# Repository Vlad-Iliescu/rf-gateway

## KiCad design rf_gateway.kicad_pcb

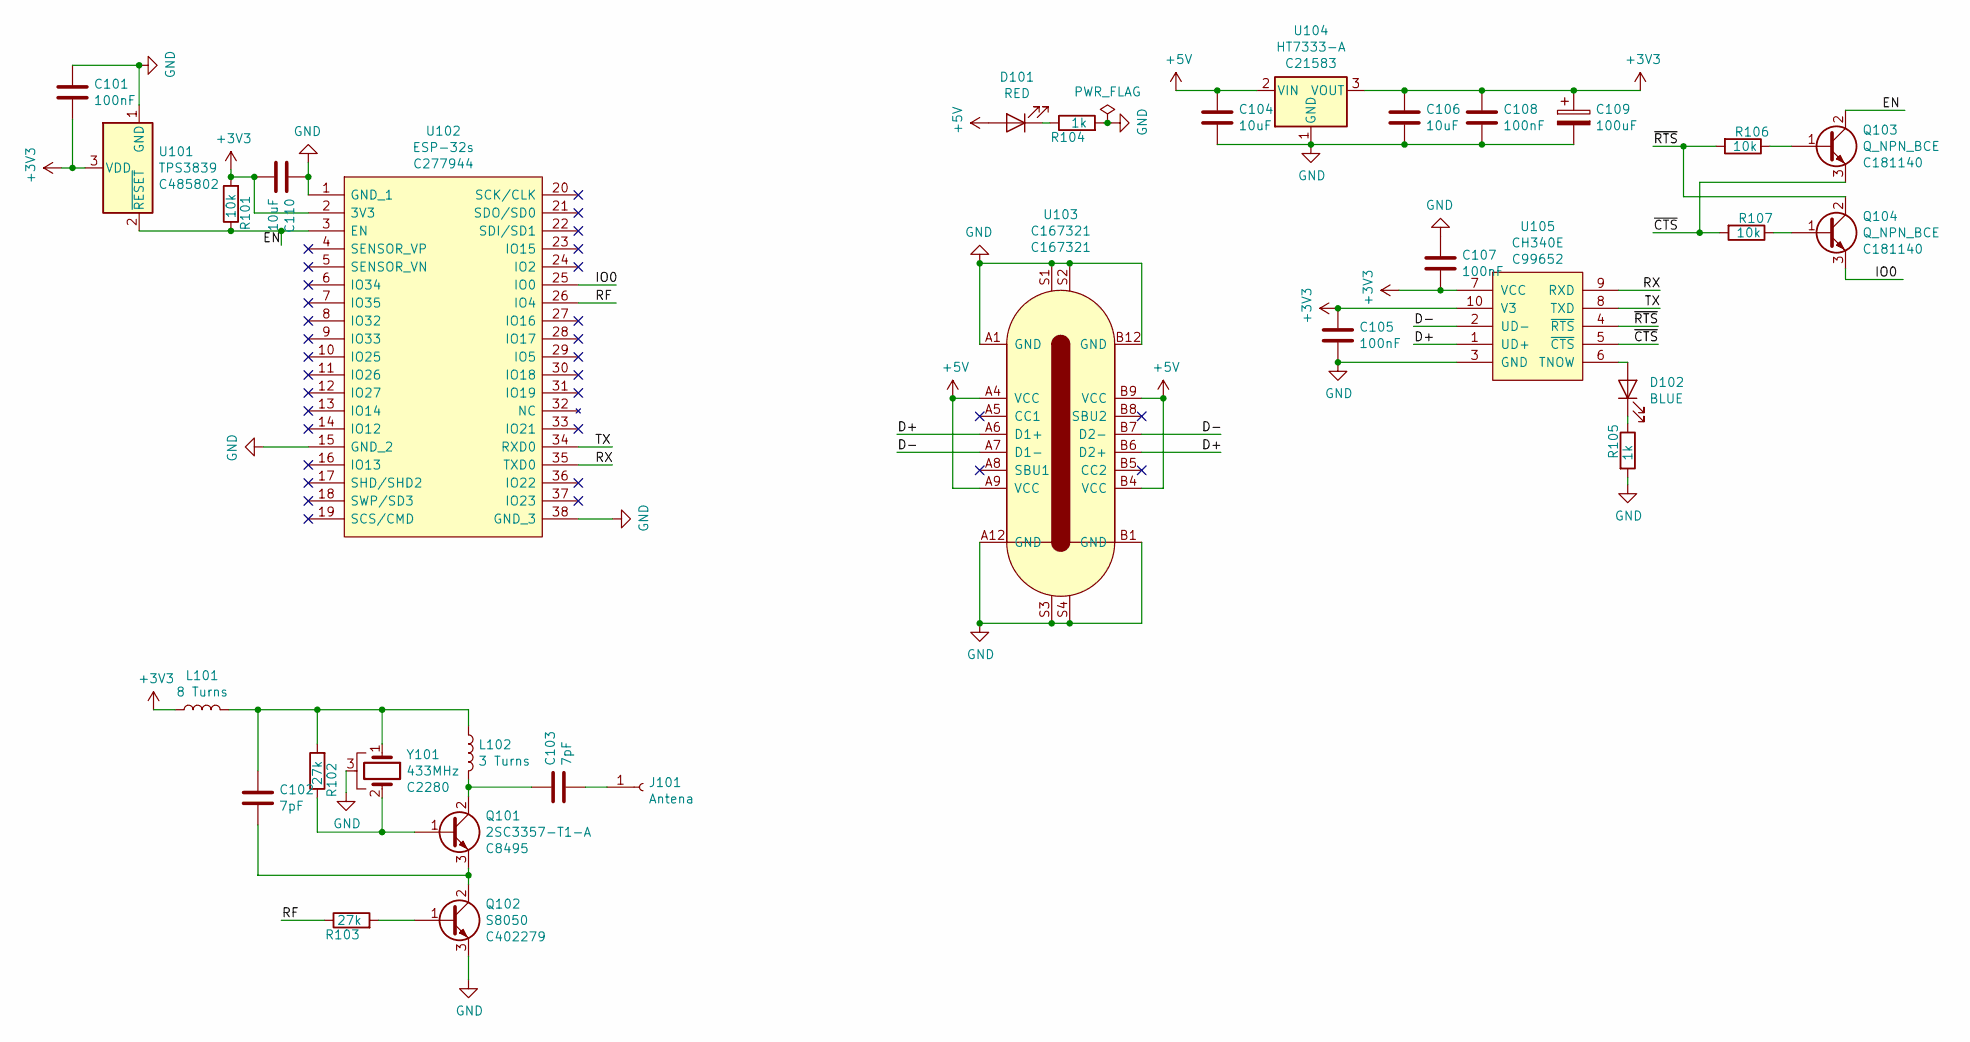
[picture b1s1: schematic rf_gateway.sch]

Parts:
C101, C105, C107, C108: 100nF; C_0805_2012Metric_Pad1.15x1.40mm_HandSolder
C102, C103: 7pF; C_0805_2012Metric_Pad1.15x1.40mm_HandSolder
C104, C106, C110: 10uF; C_0805_2012Metric_Pad1.15x1.40mm_HandSolder
C109: 100uF; TAJB107M010RNJ
D101: RED; LED_0805_2012Metric_Pad1.15x1.40mm_HandSolder
D102: BLUE; LED_0805_2012Metric_Pad1.15x1.40mm_HandSolder
J101: Antena; PinHeader_1x01_P2.54mm_Vertical
L101: 8 Turns; L_Axial_L5.3mm_D2.2mm_P7.62mm_Horizontal_Vishay_IM-1
L102: 3 Turns; L_Axial_L5.3mm_D2.2mm_P7.62mm_Horizontal_Vishay_IM-1
Q101: 2SC3357-T1-A; SOT-89-3_Handsoldering; LCSC C8495
Q102: S8050; SOT-23; LCSC C402279
Q103, Q104: Q_NPN_BCE; SOT-523; LCSC C181140
R101, R106, R107: 10k; 0805
R102, R103: 27k; 0805
R104, R105: 1k; 0805
U101: TPS3839; SOT-23; LCSC C485802
U102: ESP-32s; ESP-32S; Manufacturer_Part_Number ESP-32s; LCSC C277944
U103: C167321; LCSC C167321
U104: HT7333-A; SOT-89-3_Handsoldering; LCSC C21583
U105: CH340E; CH340E-MSOP-10; LCSC C99652
Y101: 433MHz; C2280; LCSC C2280

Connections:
+3V3: C101.2, C105.1, C106.1, C107.2, C108.1, C109.1, C110.2, L101.1, R101.2, U101.3 (VDD), U102.2 (3V3), U104.3 (VOUT), U105.7 (VCC), U105.10 (V3)
+5V: C104.1, D101.2 (A), U103.A4 (VCC), U103.A9 (VCC), U103.B4 (VCC), U103.B9 (VCC), U104.2 (VIN)
/D+: U103.A6 (D1+), U103.B6 (D2+), U105.1 (UD+)
/D-: U103.A7 (D1-), U103.B7 (D2-), U105.2 (UD-)
/EN: Q103.2 (C), R101.1, U101.2 (~RESET), U102.3 (EN)
/IO0: Q104.3 (E), U102.25 (IO0)
/RF: R103.1, U102.26 (IO4)
/RX: U102.35 (TXD0), U105.9 (RXD)
/TX: U102.34 (RXD0), U105.8 (TXD)
/~CTS: Q103.3 (E), R107.2, U105.5 (~CTS~)
/~RTS: Q104.2 (C), R106.2, U105.4 (~RTS~)
GND: C101.1, C104.2, C105.2, C106.2, C107.1, C108.2, C109.2, C110.1, Q102.3 (E), R104.2, R105.2, U101.1 (GND), U102.1 (GND_1), U102.15 (GND_2), U102.38 (GND_3), U103.A1 (GND), U103.A12 (GND), U103.B1 (GND), U103.B12 (GND), U103.S1, U103.S2, U103.S3, U103.S4, U104.1 (GND), U105.3 (GND), Y101.3
unnamed: C102.1, L101.2, L102.1, R102.2, Y101.1
unnamed: C102.2, Q101.3 (E), Q102.2 (C)
unnamed: C103.1, L102.2, Q101.2 (C)
unnamed: C103.2, J101.1
unnamed: D101.1 (K), R104.1
unnamed: D102.1 (K), R105.1
unnamed: D102.2 (A), U105.6 (TNOW)
unnamed: Q101.1 (B), R102.1, Y101.2
unnamed: Q102.1 (B), R103.2
unnamed: Q103.1 (B), R106.1
unnamed: Q104.1 (B), R107.1

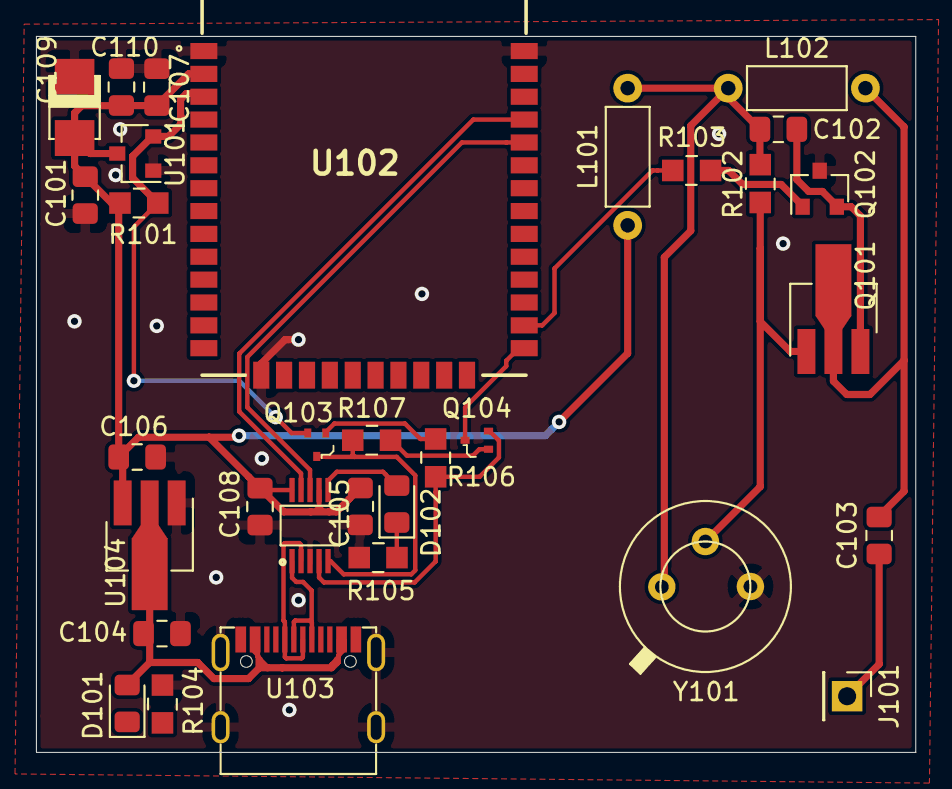
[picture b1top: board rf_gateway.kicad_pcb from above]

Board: 2 copper layers, 48.8 x 39.8 mm, 32 parts (0 on the bottom side), 23 nets.

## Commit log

2020-03-17 Init
2020-03-20 First RC
